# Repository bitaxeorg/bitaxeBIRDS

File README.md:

Bitaxe Intel Reference Design System (BIRDS) quad Intel BZM2 ASIC miner for BZM2 firmware development.

It is still an untested prototype! Don't build this expecting it to work out of the box. Do build it if you want to hack on some rad stuff.

- Open Hardware License; Real Open Source.
	- [KiCAD](https://kicad.org) design files. 
- Four Intel BZM2 ASICs, powered in series.
	- Each BZM2 is [nominally](doc/specs.md) 0.7V with approx 350 GH/s @ 1.15 GHz hash frequency.
	- On chip digital temperature and voltage sensors
	- ntime rolling
	- decent cross-domain level shifting, that _hopefully_ works. 
- 11-13V XT30 input voltage
- TPS546D24S single-phase voltage regulator tuned for 2.8V output @ 20A
	- The voltage regulator backside power plane is exposed to hopefully thermally bond it with the main heatsink. 
- New fan control strategy (no more EMC2101)
- Controlled by the [RaspberryPi Pico 2W](https://www.raspberrypi.com/products/raspberry-pi-pico-2/) featuring the RP2350 microcontroller and a Infineon CYW43439 WiFi SoC
	- Rumored to have good embedded Rust support
	- Programmable IO controller for integrating with the gnarly 5Mbaud, 9bit serial on the BZM2
    - Preliminary support with the [bitaxe-raw-pico](https://github.com/bitaxeorg/bitaxe-raw/tree/pico) firmware.
    	- Note: this targets the RP2040 in the Pico. It's pin compatible with with RP2350-based Pico 2. 
- Gerbers _not_ provided to discourage side hacks and AliEx slop. HMU if you need help generating gerbers with KiCad.

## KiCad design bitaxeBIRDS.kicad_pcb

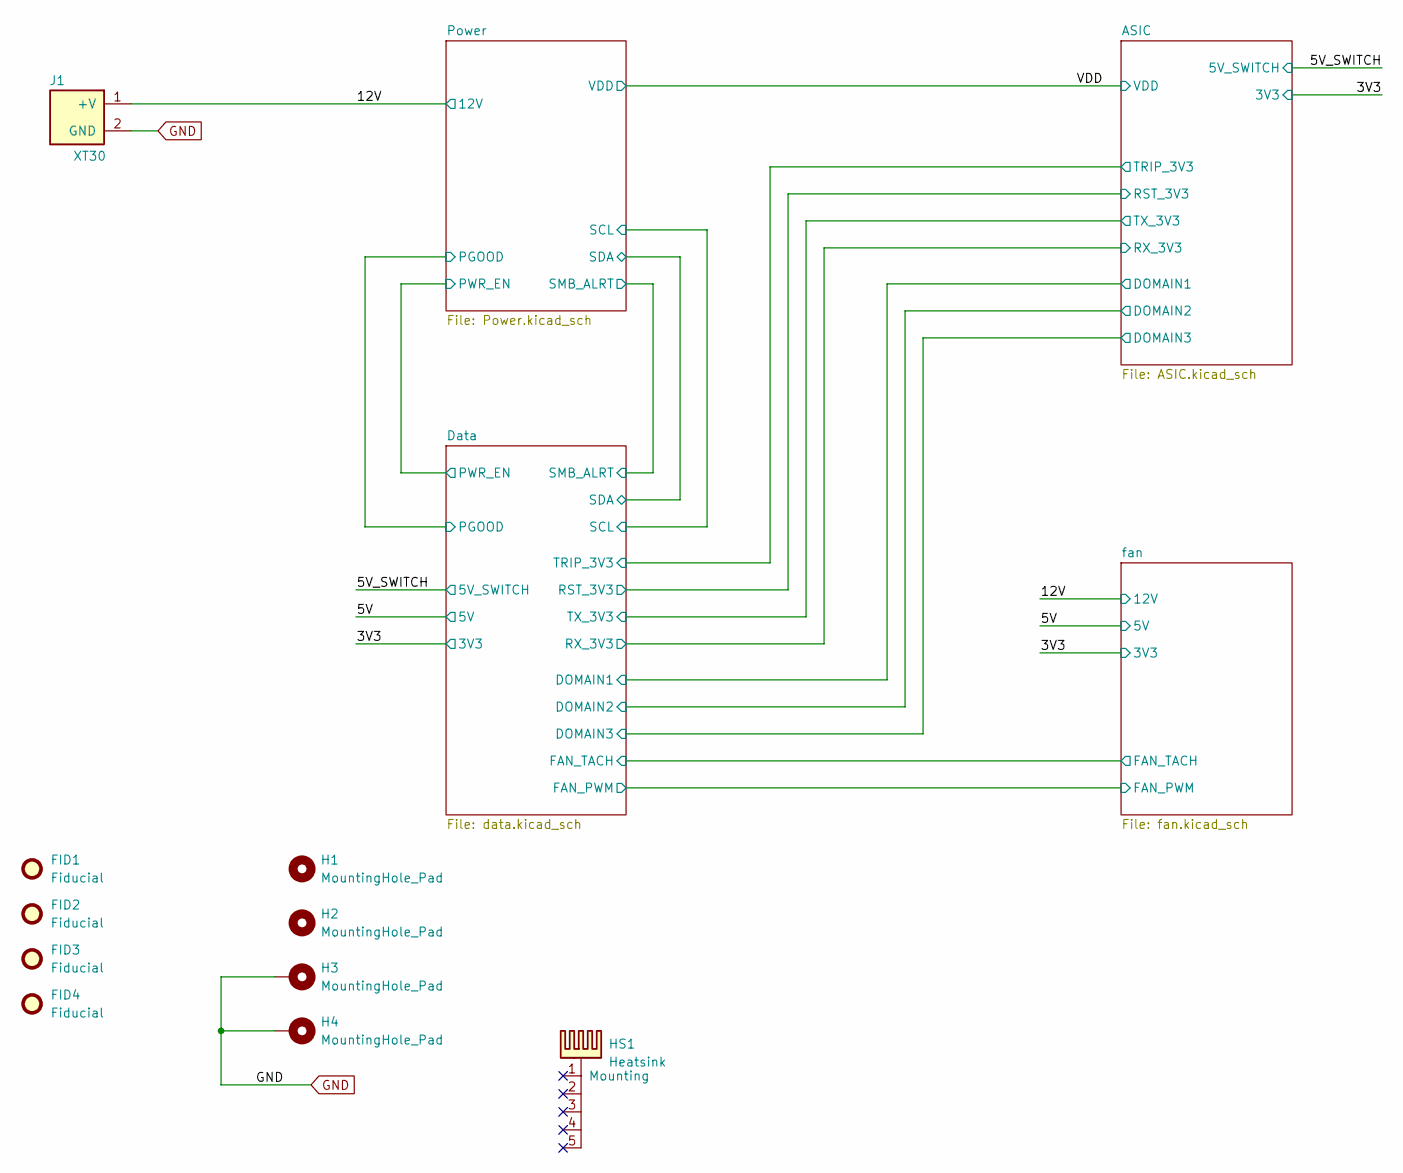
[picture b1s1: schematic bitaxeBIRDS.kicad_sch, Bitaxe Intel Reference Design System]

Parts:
FID1, FID2, FID3, FID4: Fiducial; Fiducial_1mm_Mask2mm
H1, H2: MountingHole_Pad; MountingHole_3.2mm_M3
H3, H4: MountingHole_Pad; MountingHole_3.2mm_M3_Pad_Via
HS1: Heatsink; Heatsink-5hole-BitaxeGT
J1: XT30; XT30PW-M; PARTNO XT30PW-M; LCSC C431092

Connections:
/12V: J1.1 (+V); also elsewhere on the board
GND: H3.1, H4.1, J1.2 (GND); also elsewhere on the board

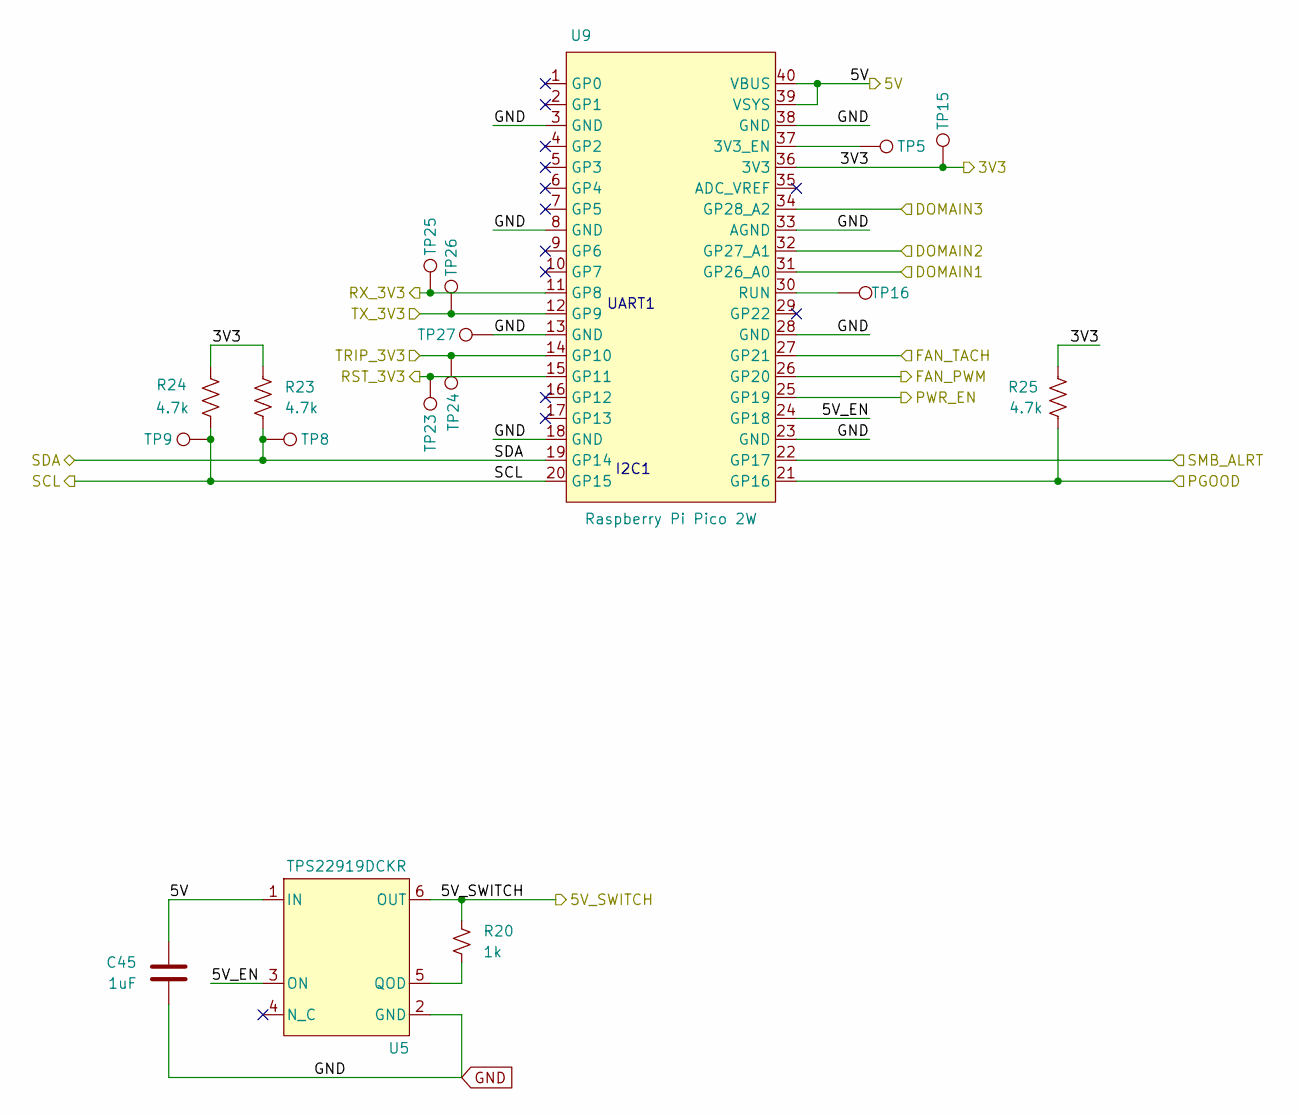
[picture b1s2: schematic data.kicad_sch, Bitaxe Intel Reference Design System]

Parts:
C45: 1uF; C_0402_1005Metric; PARTNO EMK105BJ105MV-F
R20: 1k; R_0402_1005Metric; PARTNO RC0402FR-071KL
R23, R24, R25: 4.7k; R_0402_1005Metric; PARTNO RC0402FR-074K7L
TP5: 3V3 EN; TestPoint_Pad_D1.0mm
TP8: SDA; TestPoint_Pad_D1.0mm
TP9: SCL; TestPoint_Pad_D1.0mm
TP15: 3V3; TestPoint_Pad_D1.0mm
TP16: RUN; TestPoint_Pad_D1.0mm
TP23: RST; TestPoint_Pad_D1.0mm
TP24: TT; TestPoint_Pad_D1.0mm
TP25: RX; TestPoint_Pad_D1.0mm
TP26: TX; TestPoint_Pad_D1.0mm
TP27: GND; TestPoint_Pad_D1.0mm
U5: TPS22919DCKR; DCK0006A_N; PARTNO TPS22919DCKR
U9: Raspberry Pi Pico 2W; RaspberryPi_Pico_Common_THT

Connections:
/3V3: R23.1, R24.2, R25.2, TP15.1, U9.36 (3V3); also elsewhere on the board
/5V: C45.1, U5.1 (IN), U9.39 (VSYS), U9.40 (VBUS); also elsewhere on the board
/5V_SWITCH: R20.1, U5.6 (OUT); also elsewhere on the board
/ASIC/GND2: U9.31 (GP26_A0); also elsewhere on the board
/ASIC/GND3: U9.32 (GP27_A1); also elsewhere on the board
/ASIC/GND4: U9.34 (GP28_A2); also elsewhere on the board
/ASIC/RST_3V3: TP23.1, U9.15 (GP11); also elsewhere on the board
/ASIC/RX_3V3: TP25.1, U9.11 (GP8); also elsewhere on the board
/ASIC/TRIP_3V3: TP24.1, U9.14 (GP10); also elsewhere on the board
/ASIC/TX_3V3: TP26.1, U9.12 (GP9); also elsewhere on the board
/Data/5V_EN: U5.3 (ON), U9.24 (GP18)
/Data/FAN_PWM: U9.26 (GP20); also elsewhere on the board
/Data/FAN_TACH: U9.27 (GP21); also elsewhere on the board
/Data/SCL: R24.1, TP9.1, U9.20 (GP15); also elsewhere on the board
/Data/SDA: R23.2, TP8.1, U9.19 (GP14); also elsewhere on the board
/Power/PGOOD: R25.1, U9.21 (GP16); also elsewhere on the board
/Power/PWR_EN: U9.25 (GP19); also elsewhere on the board
/Power/SMB_ALRT: U9.22 (GP17); also elsewhere on the board
GND: C45.2, TP27.1, U5.2 (GND), U9.3 (GND), U9.8 (GND), U9.13 (GND), U9.18 (GND), U9.23 (GND), U9.28 (GND), U9.33 (AGND), U9.38 (GND); also elsewhere on the board
unnamed: R20.2, U5.5 (QOD)
unnamed: TP5.1, U9.37 (3V3_EN)
unnamed: TP16.1, U9.30 (RUN)

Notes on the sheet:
UART1
I2C1

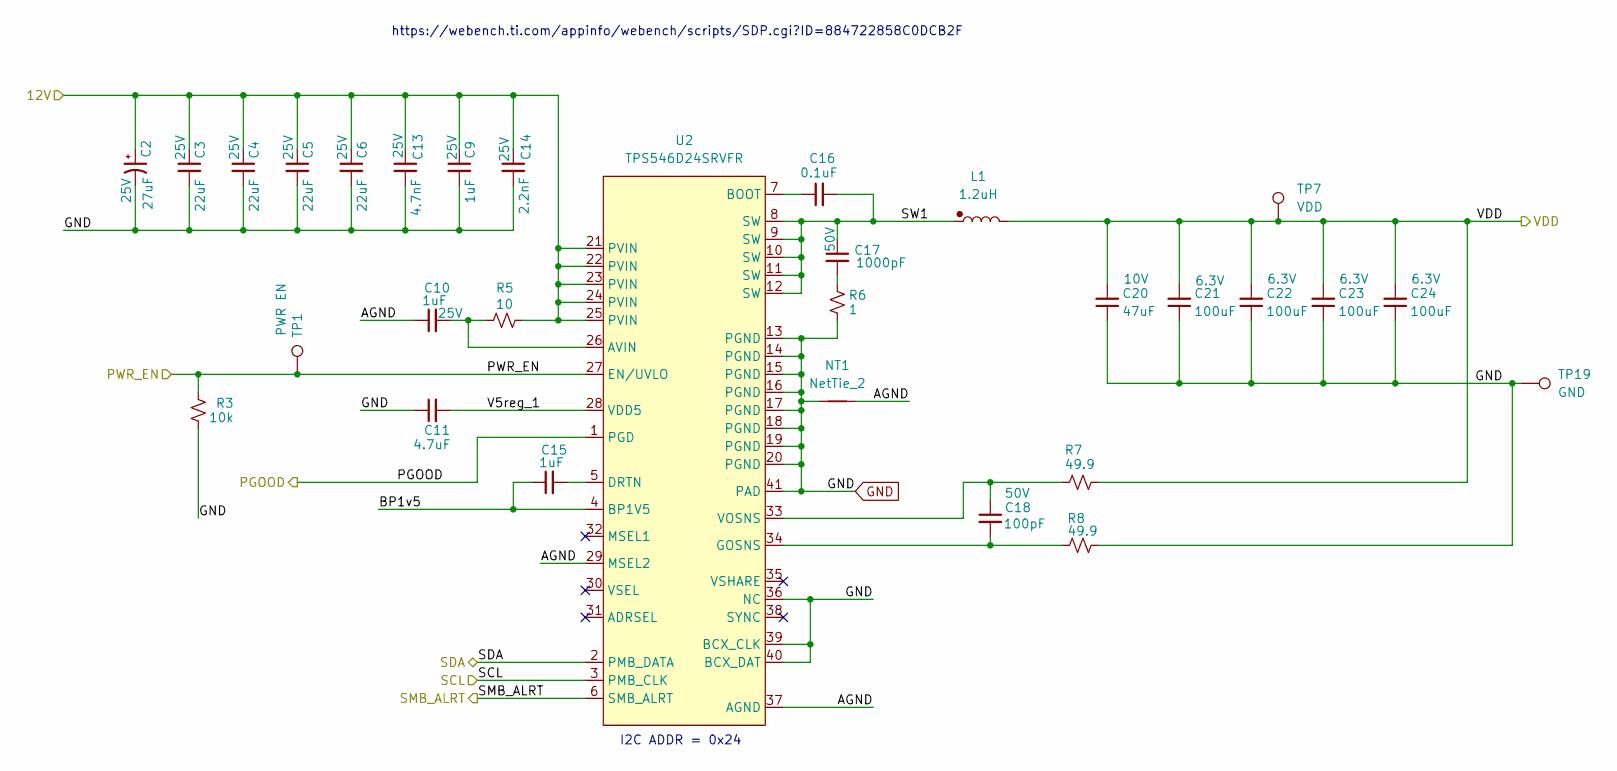
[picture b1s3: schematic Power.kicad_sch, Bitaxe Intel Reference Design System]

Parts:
C2: 27uF; CP_Elec_5x5.9; Voltage 25V; PARTNO APXG250ARA270MF46G
C3, C4, C5, C6: 22uF; C_1206_3216Metric; Voltage 25V; PARTNO TMK316BBJ226ML-T
C9, C10: 1uF; C_0603_1608Metric; Voltage 25V; PARTNO TMK107B7105KA-T
C11: 4.7uF; C_0402_1005Metric; PARTNO GRM155R61A475MEAAD
C13: 4.7nF; C_0402_1005Metric; Voltage 25V; PARTNO GRM155R71E472KA01D
C14: 2.2nF; C_0402_1005Metric; Voltage 25V; PARTNO GRM155R61H222KA01D
C15: 1uF; C_0402_1005Metric; PARTNO EMK105BJ105MV-F
C16: 0.1uF; C_0402_1005Metric; PARTNO KGM05AR71C104KH
C17: 1000pF; C_0805_2012Metric; Voltage 50V; PARTNO CC0805KRX7R9BB102
C18: 100pF; C_0402_1005Metric; Voltage 50V; PARTNO CC0402JRNPO9BN101
C20: 47uF; C_1206_3216Metric; Voltage 10V; PARTNO GRM31CR61A476ME15L
C21, C22, C23, C24: 100uF; C_1206_3216Metric; Voltage 6.3V; PARTNO CL31A107MQHNNNE
L1: 1.2uH; XAL1060122MEC; PARTNO XAL1060-122MEC
NT1: NetTie_2; NetTie-2_SMD_Pad0.2mmx1mm
R3: 10k; R_0402_1005Metric; PARTNO RC0402JR-0710KL
R5: 10; R_0402_1005Metric; PARTNO RC0402FR-0710RL
R6: 1; R_0805_2012Metric; PARTNO ESR10EZPJ1R0
R7, R8: 49.9; R_0402_1005Metric; PARTNO RC0402FR-0749R9L
TP1: PWR EN; TestPoint_Pad_D1.0mm
TP7: VDD; TestPoint_Pad_D1.0mm
TP19: GND; TestPoint_Pad_D1.0mm
U2: TPS546D24SRVFR; LQFN40-CLIP; PARTNO TPS546D24ARVFR

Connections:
/12V: C2.1, C3.1, C4.1, C5.1, C6.1, C9.1, C13.1, C14.1, R5.1, U2.21 (PVIN), U2.22 (PVIN), U2.23 (PVIN), U2.24 (PVIN), U2.25 (PVIN); also elsewhere on the board
/Data/SCL: U2.3 (PMB_CLK); also elsewhere on the board
/Data/SDA: U2.2 (PMB_DATA); also elsewhere on the board
/Power/AGND: C10.1, NT1.2, U2.29 (MSEL2), U2.37 (AGND)
/Power/BP1v5: C15.1, U2.4 (BP1V5)
/Power/PGOOD: U2.1 (PGD); also elsewhere on the board
/Power/PWR_EN: R3.2, TP1.1, U2.27 (EN/UVLO); also elsewhere on the board
/Power/SMB_ALRT: U2.6 (SMB_ALRT); also elsewhere on the board
/Power/SW1: C16.2, C17.1, L1.1, U2.8 (SW), U2.9 (SW), U2.10 (SW), U2.11 (SW), U2.12 (SW)
/Power/V5reg_1: C11.2, U2.28 (VDD5)
/VDD: C20.2, C21.2, C22.2, C23.2, C24.2, L1.2, R7.1, TP7.1; also elsewhere on the board
GND: C2.2, C3.2, C4.2, C5.2, C6.2, C9.2, C11.1, C13.2, C14.2, C20.1, C21.1, C22.1, C23.1, C24.1, NT1.1, R3.1, R6.2, R8.2, TP19.1, U2.13 (PGND), U2.14 (PGND), U2.15 (PGND), U2.16 (PGND), U2.17 (PGND), U2.18 (PGND), U2.19 (PGND), U2.20 (PGND), U2.36 (NC), U2.39 (BCX_CLK), U2.40 (BCX_DAT), U2.41 (PAD); also elsewhere on the board
unnamed: C17.2, R6.1
unnamed: C10.2, R5.2, U2.26 (AVIN)
unnamed: C16.1, U2.7 (BOOT)
unnamed: C15.2, U2.5 (DRTN)
unnamed: C18.2, R8.1, U2.34 (GOSNS)
unnamed: C18.1, R7.2, U2.33 (VOSNS)

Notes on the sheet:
I2C ADDR = 0x24
https://webench.ti.com/appinfo/webench/scripts/SDP.cgi?ID=884722858C0DCB2F

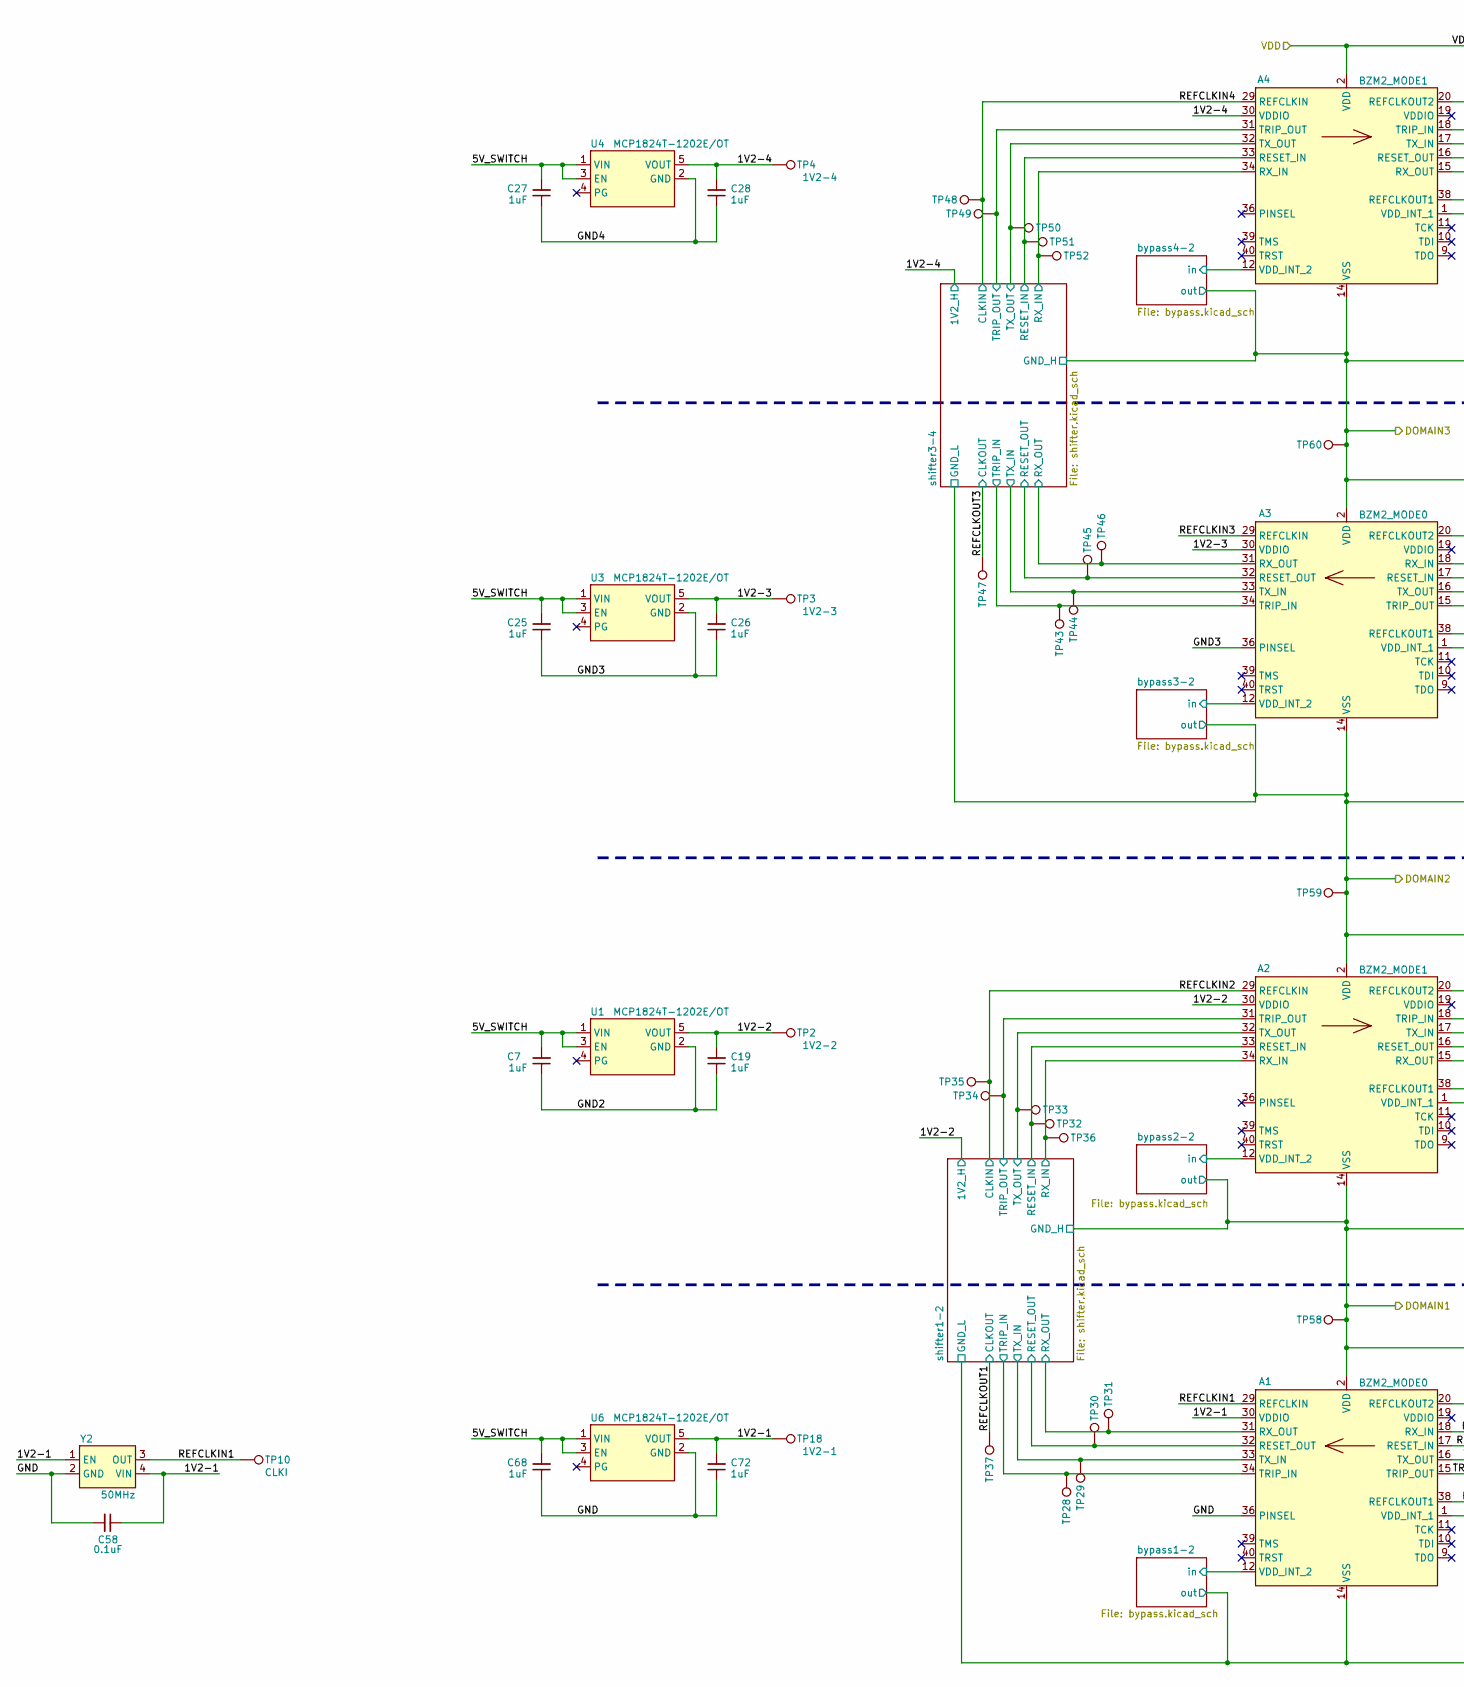
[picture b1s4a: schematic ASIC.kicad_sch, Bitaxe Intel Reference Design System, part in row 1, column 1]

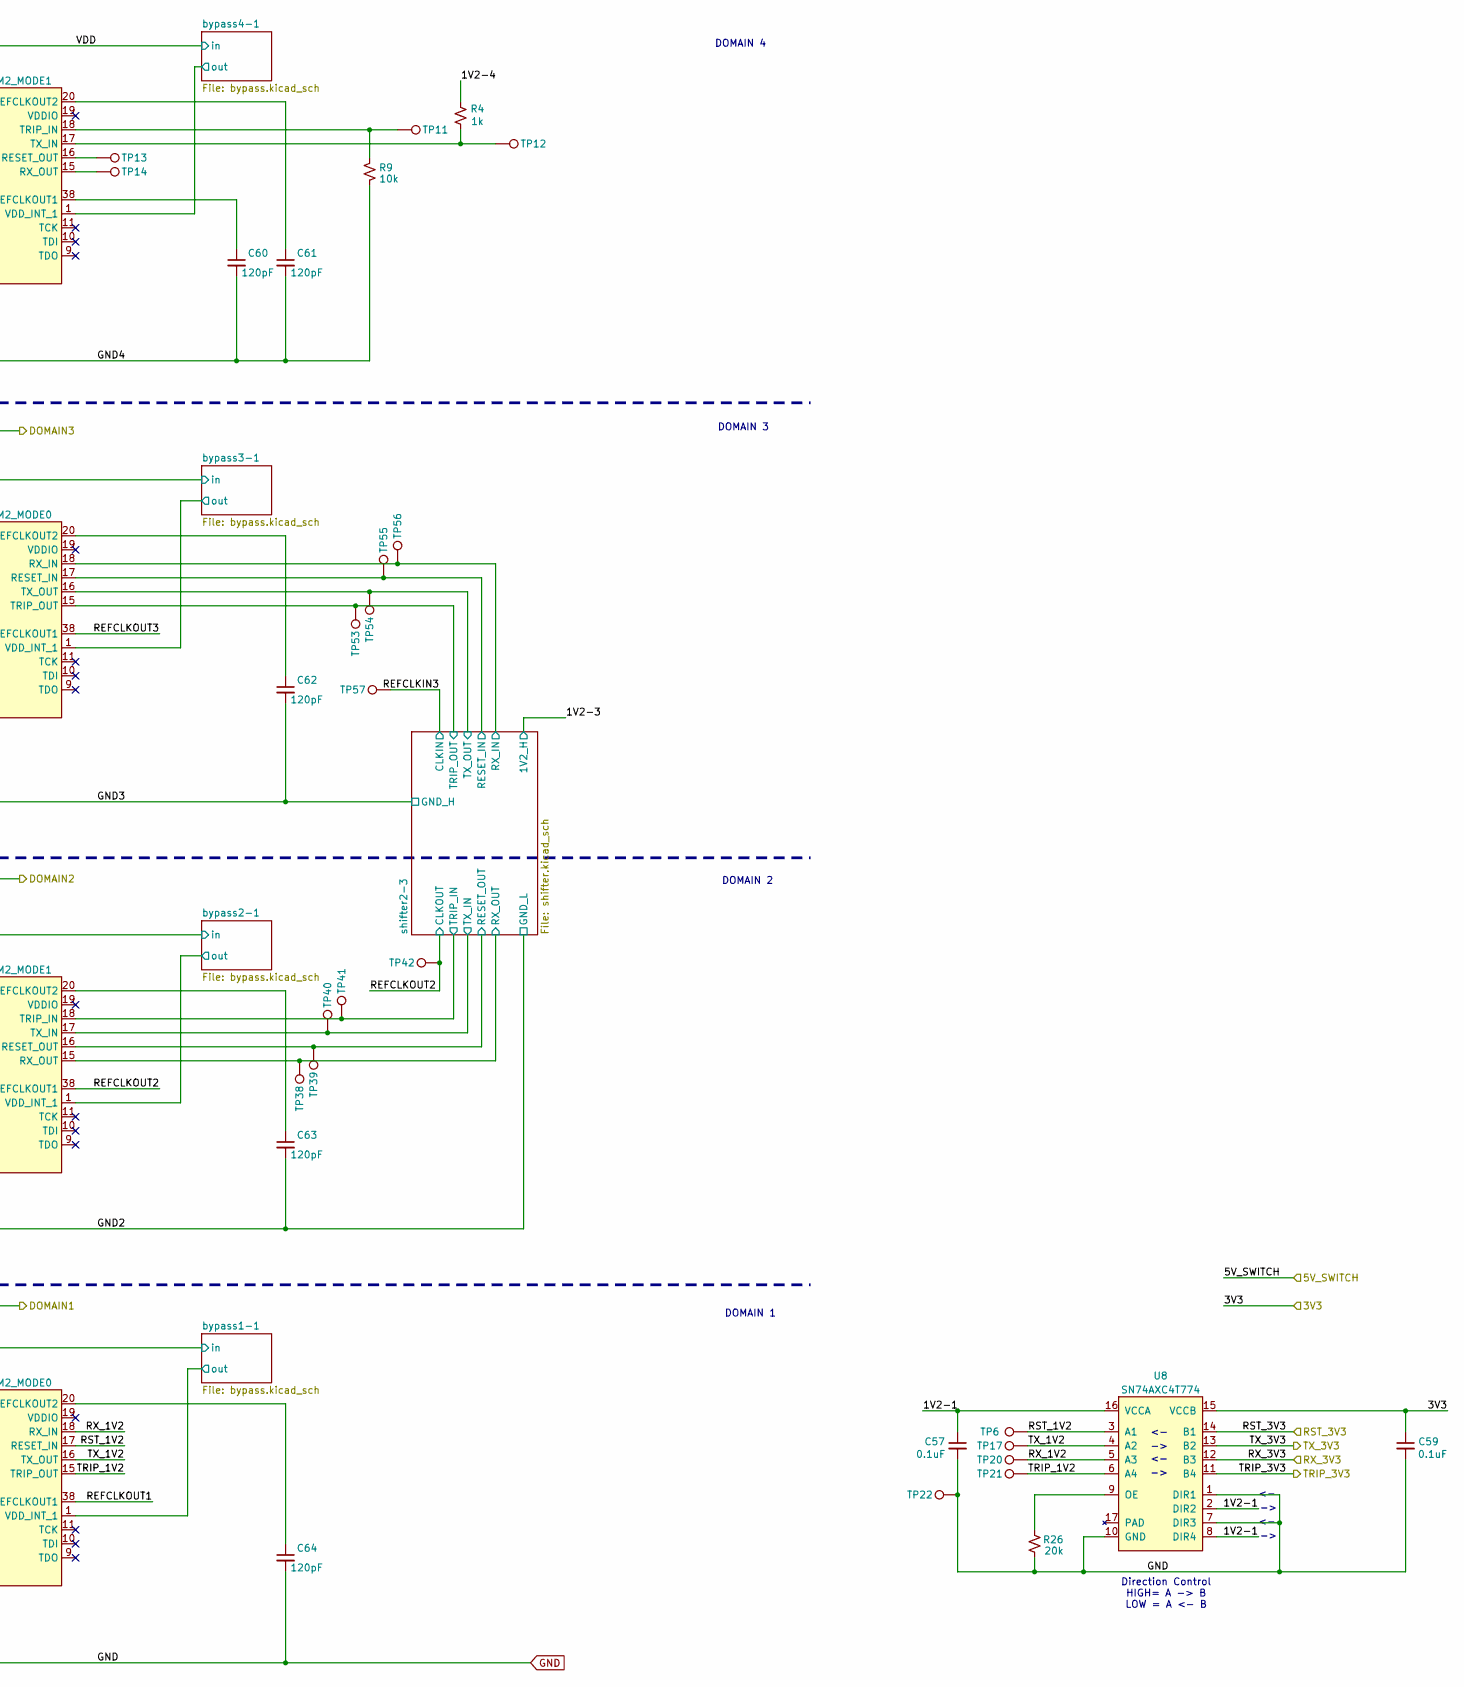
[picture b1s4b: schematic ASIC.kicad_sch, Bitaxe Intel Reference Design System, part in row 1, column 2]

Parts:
A1, A3: BZM2_MODE0; bzm2
A2, A4: BZM2_MODE1; bzm2
C7, C19, C25, C26, C27, C28, C68, C72: 1uF; C_0402_1005Metric; PARTNO EMK105BJ105MV-F
C57, C58, C59: 0.1uF; C_0402_1005Metric; PARTNO KGM05AR71C104KH
C60, C61, C62, C63, C64: 120pF; C_0402_1005Metric; PARTNO GCM1555C1H121FA16D
R4: 1k; R_0402_1005Metric; PARTNO RC0402FR-071KL
R9: 10k; R_0402_1005Metric; PARTNO RC0402JR-0710KL
R26: 20k; R_0402_1005Metric; PARTNO RC0402FR-0720KL
TP2: 1V2-2; TestPoint_Pad_D1.0mm
TP3: 1V2-3; TestPoint_Pad_D1.0mm
TP4: 1V2-4; TestPoint_Pad_D1.0mm
TP6, TP13, TP32, TP51, TP55: RSTI; TestPoint_Pad_1.0x0.4mm
TP10: CLKI; TestPoint_Pad_D1.0mm
TP11, TP28, TP43: TTI; TestPoint_Pad_1.0x0.4mm
TP12, TP29, TP44: TXI; TestPoint_Pad_1.0x0.4mm
TP14, TP31, TP38, TP46: RXO; TestPoint_Pad_1.0x0.4mm
TP17, TP33, TP40, TP50, TP54: TXO; TestPoint_Pad_1.0x0.4mm
TP18: 1V2-1; TestPoint_Pad_D1.0mm
TP20, TP36, TP52, TP56: RXI; TestPoint_Pad_1.0x0.4mm
TP21, TP34, TP41, TP49, TP53: TTO; TestPoint_Pad_1.0x0.4mm
TP22: GND; TestPoint_Pad_1.0x0.4mm
TP30, TP39, TP45: RSTO; TestPoint_Pad_1.0x0.4mm
TP35, TP48, TP57: CLKI; TestPoint_Pad_1.0x0.4mm
TP37, TP42, TP47: CLKO; TestPoint_Pad_1.0x0.4mm
TP58: D1; TestPoint_Pad_D1.0mm
TP59: D2; TestPoint_Pad_D1.0mm
TP60: D3; TestPoint_Pad_D1.0mm
U1, U3, U4, U6: MCP1824T-1202E/OT; SOT-23-5; PARTNO MCP1824T-1202E/OT
U8: SN74AXC4T774; BQB0016A-MFG; PARTNO SN74AXC4T774BQBR
Y2: 50MHz; OSC_ECS-3225MV-500-CN-TR; PARTNO SX3M50.000E20F30THN; LCSC C5137267

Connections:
/3V3: C59.1, U8.15 (VCCB); also elsewhere on the board
/5V_SWITCH: C7.2, C25.2, C27.2, C68.2, U1.1 (VIN), U1.3 (EN), U3.1 (VIN), U3.3 (EN), U4.1 (VIN), U4.3 (EN), U6.1 (VIN), U6.3 (EN); also elsewhere on the board
/ASIC/1V2-1: A1.30 (VDDIO), C57.1, C58.1, C72.2, TP18.1, U6.5 (VOUT), U8.2 (DIR2), U8.8 (DIR4), U8.16 (VCCA), Y2.1 (EN), Y2.4 (VIN)
/ASIC/1V2-2: A2.30 (VDDIO), C19.2, TP2.1, U1.5 (VOUT); also elsewhere on the board
/ASIC/1V2-3: A3.30 (VDDIO), C26.2, TP3.1, U3.5 (VOUT); also elsewhere on the board
/ASIC/1V2-4: A4.30 (VDDIO), C28.2, R4.1, TP4.1, U4.5 (VOUT); also elsewhere on the board
/ASIC/GND2: A1.2 (VDD), A1.3 (VDD), A1.4 (VDD), A1.5 (VDD), A1.6 (VDD), A1.7 (VDD), A1.8 (VDD), A1.41 (VDD), A1.42 (VDD), A1.49 (VDD), A1.50 (VDD), A1.51 (VDD), A1.52 (VDD), A1.59 (VDD), A1.60 (VDD), A2.14 (VSS), A2.21 (VSS), A2.22 (VSS), A2.23 (VSS), A2.24 (VSS), A2.25 (VSS), A2.26 (VSS), A2.27 (VSS), A2.28 (VSS), A2.35 (VSS), A2.43 (VSS), A2.44 (VSS), A2.45 (VSS), A2.46 (VSS), A2.47 (VSS), A2.48 (VSS), A2.53 (VSS), A2.54 (VSS), A2.55 (VSS), A2.56 (VSS), A2.57 (VSS), A2.58 (VSS), C7.1, C19.1, C63.2, TP58.1, U1.2 (GND); also elsewhere on the board
/ASIC/GND3: A2.2 (VDD), A2.3 (VDD), A2.4 (VDD), A2.5 (VDD), A2.6 (VDD), A2.7 (VDD), A2.8 (VDD), A2.41 (VDD), A2.42 (VDD), A2.49 (VDD), A2.50 (VDD), A2.51 (VDD), A2.52 (VDD), A2.59 (VDD), A2.60 (VDD), A3.14 (VSS), A3.21 (VSS), A3.22 (VSS), A3.23 (VSS), A3.24 (VSS), A3.25 (VSS), A3.26 (VSS), A3.27 (VSS), A3.28 (VSS), A3.35 (VSS), A3.36 (PINSEL), A3.43 (VSS), A3.44 (VSS), A3.45 (VSS), A3.46 (VSS), A3.47 (VSS), A3.48 (VSS), A3.53 (VSS), A3.54 (VSS), A3.55 (VSS), A3.56 (VSS), A3.57 (VSS), A3.58 (VSS), C25.1, C26.1, C62.2, TP59.1, U3.2 (GND); also elsewhere on the board
/ASIC/GND4: A3.2 (VDD), A3.3 (VDD), A3.4 (VDD), A3.5 (VDD), A3.6 (VDD), A3.7 (VDD), A3.8 (VDD), A3.41 (VDD), A3.42 (VDD), A3.49 (VDD), A3.50 (VDD), A3.51 (VDD), A3.52 (VDD), A3.59 (VDD), A3.60 (VDD), A4.14 (VSS), A4.21 (VSS), A4.22 (VSS), A4.23 (VSS), A4.24 (VSS), A4.25 (VSS), A4.26 (VSS), A4.27 (VSS), A4.28 (VSS), A4.35 (VSS), A4.43 (VSS), A4.44 (VSS), A4.45 (VSS), A4.46 (VSS), A4.47 (VSS), A4.48 (VSS), A4.53 (VSS), A4.54 (VSS), A4.55 (VSS), A4.56 (VSS), A4.57 (VSS), A4.58 (VSS), C27.1, C28.1, C60.2, C61.2, R9.2, TP60.1, U4.2 (GND); also elsewhere on the board
/ASIC/REFCLKIN1: A1.29 (REFCLKIN), TP10.1, Y2.3 (OUT)
/ASIC/REFCLKIN2: A2.29 (REFCLKIN), TP35.1; also elsewhere on the board
/ASIC/REFCLKIN3: A3.29 (REFCLKIN), TP57.1; also elsewhere on the board
/ASIC/REFCLKIN4: A4.29 (REFCLKIN), TP48.1; also elsewhere on the board
/ASIC/REFCLKOUT1: A1.38 (REFCLKOUT1), TP37.1; also elsewhere on the board
/ASIC/REFCLKOUT2: A2.38 (REFCLKOUT1), TP42.1; also elsewhere on the board
/ASIC/REFCLKOUT3: A3.38 (REFCLKOUT1), TP47.1; also elsewhere on the board
/ASIC/RST_1V2: A1.17 (RESET_IN), TP6.1, U8.3 (A1)
/ASIC/RST_3V3: U8.14 (B1); also elsewhere on the board
/ASIC/RX_1V2: A1.18 (RX_IN), TP20.1, U8.5 (A3)
/ASIC/RX_3V3: U8.12 (B3); also elsewhere on the board
/ASIC/TRIP_1V2: A1.15 (TRIP_OUT), TP21.1, U8.6 (A4)
/ASIC/TRIP_3V3: U8.11 (B4); also elsewhere on the board
/ASIC/TX_1V2: A1.16 (TX_OUT), TP17.1, U8.4 (A2)
/ASIC/TX_3V3: U8.13 (B2); also elsewhere on the board
/ASIC/bypass1-1/out: A1.1 (VDD_INT_1); also elsewhere on the board
/ASIC/bypass1-2/in: A1.12 (VDD_INT_2); also elsewhere on the board
/ASIC/bypass2-1/out: A2.1 (VDD_INT_1); also elsewhere on the board
/ASIC/bypass2-2/in: A2.12 (VDD_INT_2); also elsewhere on the board
/ASIC/bypass3-1/out: A3.1 (VDD_INT_1); also elsewhere on the board
/ASIC/bypass3-2/in: A3.12 (VDD_INT_2); also elsewhere on the board
/ASIC/bypass4-1/out: A4.1 (VDD_INT_1); also elsewhere on the board
/ASIC/bypass4-2/in: A4.12 (VDD_INT_2); also elsewhere on the board
/ASIC/shifter1-2/RESET_IN: A2.33 (RESET_IN), TP32.1; also elsewhere on the board
/ASIC/shifter1-2/RESET_OUT: A1.32 (RESET_OUT), TP30.1; also elsewhere on the board
/ASIC/shifter1-2/RX_IN: A2.34 (RX_IN), TP36.1; also elsewhere on the board
/ASIC/shifter1-2/RX_OUT: A1.31 (RX_OUT), TP31.1; also elsewhere on the board
/ASIC/shifter1-2/TRIP_IN: A1.34 (TRIP_IN), TP28.1; also elsewhere on the board
/ASIC/shifter1-2/TRIP_OUT: A2.31 (TRIP_OUT), TP34.1; also elsewhere on the board
/ASIC/shifter1-2/TX_IN: A1.33 (TX_IN), TP29.1; also elsewhere on the board
/ASIC/shifter1-2/TX_OUT: A2.32 (TX_OUT), TP33.1; also elsewhere on the board
/ASIC/shifter2-3/RESET_IN: A3.17 (RESET_IN), TP55.1; also elsewhere on the board
/ASIC/shifter2-3/RESET_OUT: A2.16 (RESET_OUT), TP39.1; also elsewhere on the board
/ASIC/shifter2-3/RX_IN: A3.18 (RX_IN), TP56.1; also elsewhere on the board
/ASIC/shifter2-3/RX_OUT: A2.15 (RX_OUT), TP38.1; also elsewhere on the board
/ASIC/shifter2-3/TRIP_IN: A2.18 (TRIP_IN), TP41.1; also elsewhere on the board
/ASIC/shifter2-3/TRIP_OUT: A3.15 (TRIP_OUT), TP53.1; also elsewhere on the board
/ASIC/shifter2-3/TX_IN: A2.17 (TX_IN), TP40.1; also elsewhere on the board
/ASIC/shifter2-3/TX_OUT: A3.16 (TX_OUT), TP54.1; also elsewhere on the board
/ASIC/shifter3-4/RESET_IN: A4.33 (RESET_IN), TP51.1; also elsewhere on the board
/ASIC/shifter3-4/RESET_OUT: A3.32 (RESET_OUT), TP45.1; also elsewhere on the board
/ASIC/shifter3-4/RX_IN: A4.34 (RX_IN), TP52.1; also elsewhere on the board
/ASIC/shifter3-4/RX_OUT: A3.31 (RX_OUT), TP46.1; also elsewhere on the board
/ASIC/shifter3-4/TRIP_IN: A3.34 (TRIP_IN), TP43.1; also elsewhere on the board
/ASIC/shifter3-4/TRIP_OUT: A4.31 (TRIP_OUT), TP49.1; also elsewhere on the board
/ASIC/shifter3-4/TX_IN: A3.33 (TX_IN), TP44.1; also elsewhere on the board
/ASIC/shifter3-4/TX_OUT: A4.32 (TX_OUT), TP50.1; also elsewhere on the board
/VDD: A4.2 (VDD), A4.3 (VDD), A4.4 (VDD), A4.5 (VDD), A4.6 (VDD), A4.7 (VDD), A4.8 (VDD), A4.41 (VDD), A4.42 (VDD), A4.49 (VDD), A4.50 (VDD), A4.51 (VDD), A4.52 (VDD), A4.59 (VDD), A4.60 (VDD); also elsewhere on the board
GND: A1.14 (VSS), A1.21 (VSS), A1.22 (VSS), A1.23 (VSS), A1.24 (VSS), A1.25 (VSS), A1.26 (VSS), A1.27 (VSS), A1.28 (VSS), A1.35 (VSS), A1.36 (PINSEL), A1.43 (VSS), A1.44 (VSS), A1.45 (VSS), A1.46 (VSS), A1.47 (VSS), A1.48 (VSS), A1.53 (VSS), A1.54 (VSS), A1.55 (VSS), A1.56 (VSS), A1.57 (VSS), A1.58 (VSS), C57.2, C58.2, C59.2, C64.2, C68.1, C72.1, R26.1, TP22.1, U6.2 (GND), U8.1 (DIR1), U8.7 (DIR3), U8.10 (GND), Y2.2 (GND); also elsewhere on the board
unnamed: A1.20 (REFCLKOUT2), C64.1
unnamed: A2.20 (REFCLKOUT2), C63.1
unnamed: A3.20 (REFCLKOUT2), C62.1
unnamed: A4.38 (REFCLKOUT1), C60.1
unnamed: A4.20 (REFCLKOUT2), C61.1
unnamed: A4.16 (RESET_OUT), TP13.1
unnamed: A4.15 (RX_OUT), TP14.1
unnamed: A4.18 (TRIP_IN), R9.1, TP11.1
unnamed: A4.17 (TX_IN), R4.2, TP12.1
unnamed: R26.2, U8.9 (OE)

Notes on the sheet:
DOMAIN 3
DOMAIN 2
Direction Control HIGH= A -> B LOW = A <- B
DOMAIN 4
DOMAIN 1

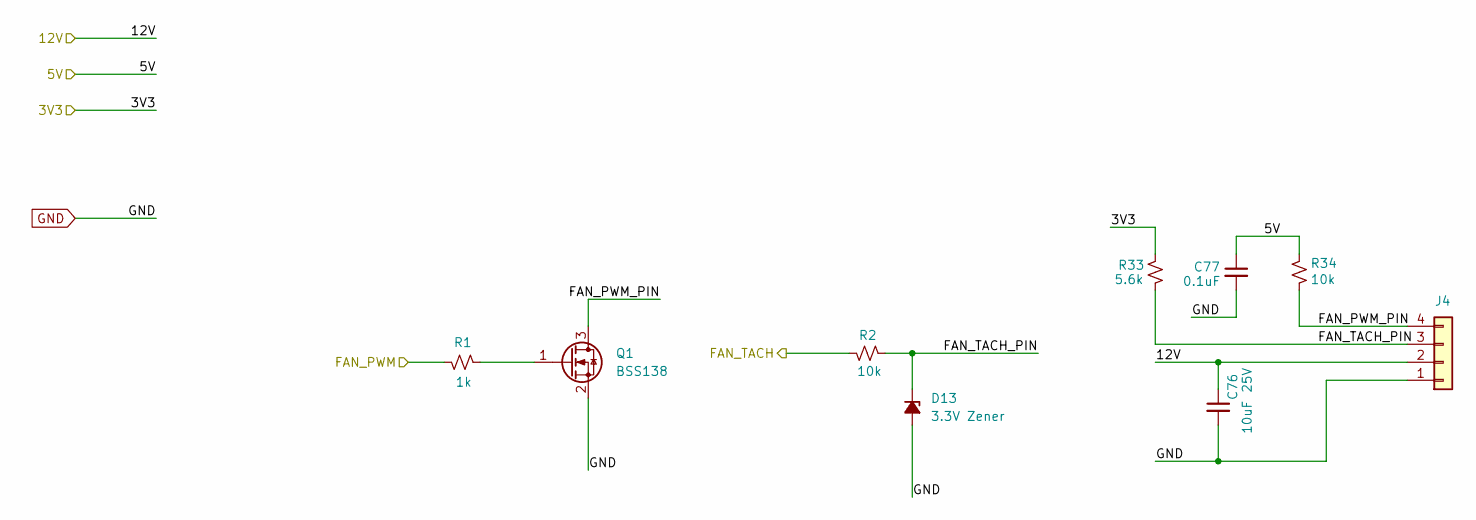
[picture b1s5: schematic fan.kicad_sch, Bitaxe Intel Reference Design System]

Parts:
C76: 10uF; C_0603_1608Metric; Voltage 25V; PARTNO GRM188R61E106KA73D
C77: 0.1uF; C_0402_1005Metric; PARTNO KGM05AR71C104KH
D13: 3.3V Zener; D_SOD-123; PARTNO DDZ9684-7
J4: Conn_01x04; 470531000; PARTNO 0470531000
Q1: BSS138; SOT-23; PARTNO BSS138K-13
R1: 1k; R_0402_1005Metric; PARTNO RC0402FR-071KL
R2, R34: 10k; R_0402_1005Metric; PARTNO RC0402JR-0710KL
R33: 5.6k; R_0402_1005Metric; PARTNO RC0402FR-075K6L

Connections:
/3V3: R33.2; also elsewhere on the board
/5V: C77.1, R34.2; also elsewhere on the board
/12V: C76.1, J4.2; also elsewhere on the board
/Data/FAN_PWM: R1.2; also elsewhere on the board
/Data/FAN_TACH: R2.2; also elsewhere on the board
/fan/FAN_PWM_PIN: J4.4, Q1.3 (D), R34.1
/fan/FAN_TACH_PIN: D13.1 (K), J4.3, R2.1, R33.1
GND: C76.2, C77.2, D13.2 (A), J4.1, Q1.2 (S); also elsewhere on the board
unnamed: Q1.1 (G), R1.1

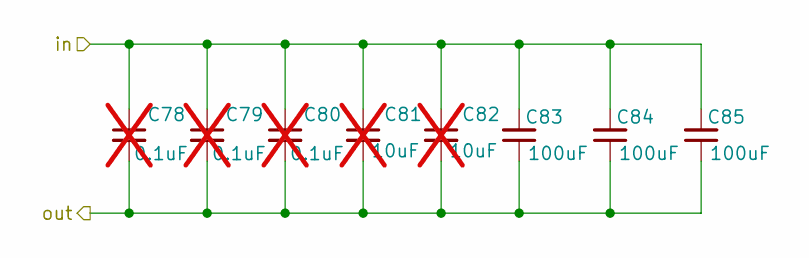
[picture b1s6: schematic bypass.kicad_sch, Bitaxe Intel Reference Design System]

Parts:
C78, C79, C80: 0.1uF; C_0402_1005Metric; PARTNO 0402X104K100CT; not fitted
C81, C82: 10uF; C_0603_1608Metric; PARTNO GRM188R61E106KA73D; not fitted
C83, C84, C85: 100uF; C_0805_2012Metric; voltage 4V; PARTNO GRM21BR60G107ME11K

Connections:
/ASIC/GND2: C83.2, C84.2, C85.2; also elsewhere on the board
/ASIC/bypass1-1/out: C83.1, C84.1, C85.1; also elsewhere on the board

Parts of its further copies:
C91, C92, C93, C99, C100, C101, C107, C108, C109, C115, C116, C117, C123, C124, C125, C131, C132, C133, C139, C140, C141: 100uF; C_0805_2012Metric; voltage 4V; PARTNO GRM21BR60G107ME11K

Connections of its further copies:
/ASIC/GND2: C107.1, C108.1, C109.1; also elsewhere on the board
/ASIC/GND3: C99.2, C100.2, C101.2, C123.1, C124.1, C125.1; also elsewhere on the board
/ASIC/GND4: C115.2, C116.2, C117.2, C139.1, C140.1, C141.1; also elsewhere on the board
/ASIC/bypass1-2/in: C91.2, C92.2, C93.2; also elsewhere on the board
/ASIC/bypass2-1/out: C99.1, C100.1, C101.1; also elsewhere on the board
/ASIC/bypass2-2/in: C107.2, C108.2, C109.2; also elsewhere on the board
/ASIC/bypass3-1/out: C115.1, C116.1, C117.1; also elsewhere on the board
/ASIC/bypass3-2/in: C123.2, C124.2, C125.2; also elsewhere on the board
/ASIC/bypass4-1/out: C131.1, C132.1, C133.1; also elsewhere on the board
/ASIC/bypass4-2/in: C139.2, C140.2, C141.2; also elsewhere on the board
/VDD: C131.2, C132.2, C133.2; also elsewhere on the board
GND: C91.1, C92.1, C93.1; also elsewhere on the board
